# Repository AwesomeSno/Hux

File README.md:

# Hux

A desktop AI smart home companion built with an ESP32-S3, featuring an animated expressive face display, an addressable RGB status ring, dual I2S voice I/O, and native local integration with Home Assistant. Inspired by Jarvis from Iron Man.

---

## What is this?

Most smart home speakers on the market are completely lifeless: they are just boring black plastic pucks sitting on your desk that listen to you with zero personality and no visual feedback beyond a single blinking LED.

For Hack Club's Half Life, I wanted to build something with actual life and presence on my desk: **Hux**. It's a custom desktop hardware companion powered by an ESP32-S3 microcontroller with a crisp color IPS display running expressive animated eyes and reactive facial emotions. 

When you speak to Hux or trigger automations around your room, it talks back, controls your Home Assistant entities (lights, plugs, AC, media) over local Wi-Fi, and dynamically switches its screen into a live telemetry HUD showing room sensor readings, weather, or device toggles.

---

## How it works

1. **Expressive Face & Telemetry Display**: A 1.69" / 2.0" ST7789 IPS LCD (240×280) sits in the center of the board, rendering smooth animated eye expressions (idle blinking, attentive listening, thinking, and speaking waveforms). When you ask about your room or devices, the screen smoothly docks into live Home Assistant glance cards.
2. **Arc-Reactor Status Halo**: A circular ring of 8 addressable RGB NeoPixels encircles the display bezel. It pulses cyan when listening, spins amber when thinking, and flashes red on sensor alerts, giving the desk unit a real presence.
3. **Local Home Assistant Integration**: Hux talks directly to Home Assistant using native WebSockets and REST APIs over local Wi-Fi. No slow cloud hops, no proprietary subscriptions: just instant local control over lights, switches, and smart entities.
4. **I2S Digital Voice Pipeline**: For voice input, an INMP441 digital MEMS microphone samples audio through a front-facing acoustic sound port drilled through the PCB. For voice replies, a MAX98357A I2S Class-D DAC amplifier powers an onboard 3W micro speaker.
5. **72mm Desktop Form Factor**: The whole system is packaged onto a 72mm × 72mm 2-layer PCB with rounded corners and M3 mounting holes, powered cleanly over USB-C.

---

## Hardware Architecture

| Component | Part / Spec | Role |
|---|---|---|
| **MCU** | ESP32-S3-WROOM-1 (16MB Flash, 8MB PSRAM) | Dual-core 240MHz controller handling Wi-Fi, display, and dual I2S audio |
| **Display** | 1.69" or 2.0" ST7789 IPS SPI LCD (240×280) | Animated vector face and smart home telemetry cards |
| **Microphone** | INMP441 I2S Digital MEMS Mic | High-SNR voice input with front acoustic port |
| **Audio Out** | MAX98357A I2S Class-D DAC + 3W 4Ω Speaker | Voice synthesis and feedback playback |
| **Halo Lighting** | 8x SK6812 MINI-E Addressable RGB LEDs | Circular Arc-Reactor status glow |
| **Power & Circuit** | USB-C 16-pin, TLV75533 3.3V LDO, USBLC6-2SC6 ESD | Clean desktop USB 5V power and transient ESD protection |
| **Dimensions** | 72mm × 72mm × 1.6mm FR4 (6mm corner radii) | Standard M3 standoff mounting holes |

---

## Schematic & Hardware Design

The hardware is designed as a clean 2-layer board in KiCad 10:

All hardware design and manufacturing files are located in [`kicad/`](kicad/):
- Full Project: [`kicad/hux.kicad_pro`](kicad/hux.kicad_pro)
- Schematic: [`kicad/hux.kicad_sch`](kicad/hux.kicad_sch) (Printable: [`kicad/hux_schematic.pdf`](kicad/hux_schematic.pdf))
- PCB Layout: [`kicad/hux.kicad_pcb`](kicad/hux.kicad_pcb)
- Bill of Materials: [`kicad/bom.csv`](kicad/bom.csv) (JLCPCB pre-formatted with LCSC parts)
- Pick & Place: [`kicad/cpl.csv`](kicad/cpl.csv)
- Production Gerbers: [`kicad/hux_gerbers.zip`](kicad/hux_gerbers.zip)

---

## Components & Bill of Materials

| Item | Part / Designation | Supplier Code (LCSC / Mfg) | Package | Qty | Role |
|---|---|---|---|---|---|
| **Microcontroller** | ESP32-S3-WROOM-1-N16R8 | LCSC: C5180337 | SMD Module | 1 | 240MHz dual-core MCU, 16MB Flash, 8MB PSRAM, Wi-Fi & BLE |
| **Color IPS Display** | ST7789 1.69" / 2.0" IPS LCD | LCSC: C2903565 / ST7789V | 8-Pin Header / SPI | 1 | Expressive face animations & telemetry dashboard |
| **Digital MEMS Mic** | INMP441 | LCSC: C444583 | SMD Acoustic | 1 | Omnidirectional I2S microphone for voice commands |
| **Audio Amplifier** | MAX98357AETE+T | LCSC: C268261 | QFN-16 | 1 | 3.2W Mono Class-D I2S DAC amplifier |
| **Micro Speaker** | 4Ω 3W Cavity Speaker | JST-PH 2.0mm / C131337 | 28mm / 31mm | 1 | Voice responses and sound effects |
| **Arc-Reactor Halo** | SK6812 MINI-E | LCSC: C2890040 | SMD-3535 | 8 | Circular addressable RGB NeoPixels for status cues |
| **Voltage Regulator** | TLV75533PDBVR | LCSC: C397683 | SOT-23-5 | 1 | Low-dropout 3.3V 500mA LDO regulator |
| **ESD Protection** | USBLC6-2SC6 | LCSC: C7519 | SOT-23-6 | 1 | High-speed USB D+/D- transient ESD suppressor |
| **USB-C Receptacle** | TYPE-C-31-M-12 (16-Pin) | LCSC: C165948 | 16-Pin SMD | 1 | 5V DC power and native USB-CDC programming |
| **Tactile Buttons** | TL3342F160QG | LCSC: C318884 | SMD SPST | 2 | Hardware Reset (EN) and Bootloader (IO0) |
| **Ceramic Capacitors** | 10µF 16V X7R (0805) | LCSC: C15849 | 0805 | 3 | Bulk power input/output filters |
| **Decoupling Caps** | 100nF 50V X7R (0805) | LCSC: C14663 | 0805 | 11 | IC supply decoupling & LED smoothing |
| **Resistors** | 5.1kΩ 1% (0805) | LCSC: C17704 | 0805 | 2 | USB-C CC1/CC2 5V pull-downs |
| **Resistors** | 10kΩ 1% (0805) | LCSC: C17414 | 0805 | 3 | Pull-ups for EN, BOOT, SD_MODE |
| **Resistors** | 330Ω 1% (0805) | LCSC: C17632 | 0805 | 1 | NeoPixel DIN data line protection |
| **Telemetry Header** | 4-Pin 2.54mm Header | LCSC: C22548 | 1x04 P2.54mm | 1 | I2C sensor expansion (SDA, SCL, 3V3, GND) |

---

## Firmware & Software Architecture

The firmware is written in modular C++ targeting the ESP32-S3 dual-core microcontroller, supporting both PlatformIO and the Arduino IDE:

- Entry Point: [`firmware/hux_firmware.ino`](firmware/hux_firmware.ino)
- PlatformIO Project: [`firmware/platformio.ini`](firmware/platformio.ini)
- Hardware Pin Config: [`firmware/include/config.h`](firmware/include/config.h)
- 60fps Vector Eye Engine: [`firmware/src/eyes.cpp`](firmware/src/eyes.cpp)
- Arc-Reactor NeoPixel Halo: [`firmware/src/halo.cpp`](firmware/src/halo.cpp)
- Dual I2S Audio Driver (Mic & Amp): [`firmware/src/audio.cpp`](firmware/src/audio.cpp)
- Home Assistant WebSocket Client: [`firmware/src/home_assistant.cpp`](firmware/src/home_assistant.cpp)
- Multithreaded Core Engine: [`firmware/src/main.cpp`](firmware/src/main.cpp)
- Firmware Guide: [`firmware/README.md`](firmware/README.md)

---

## Author

Designed and built by **Harinandan J V** ([@AwesomeSno](https://github.com/AwesomeSno)) for Hack Club's Half Life.

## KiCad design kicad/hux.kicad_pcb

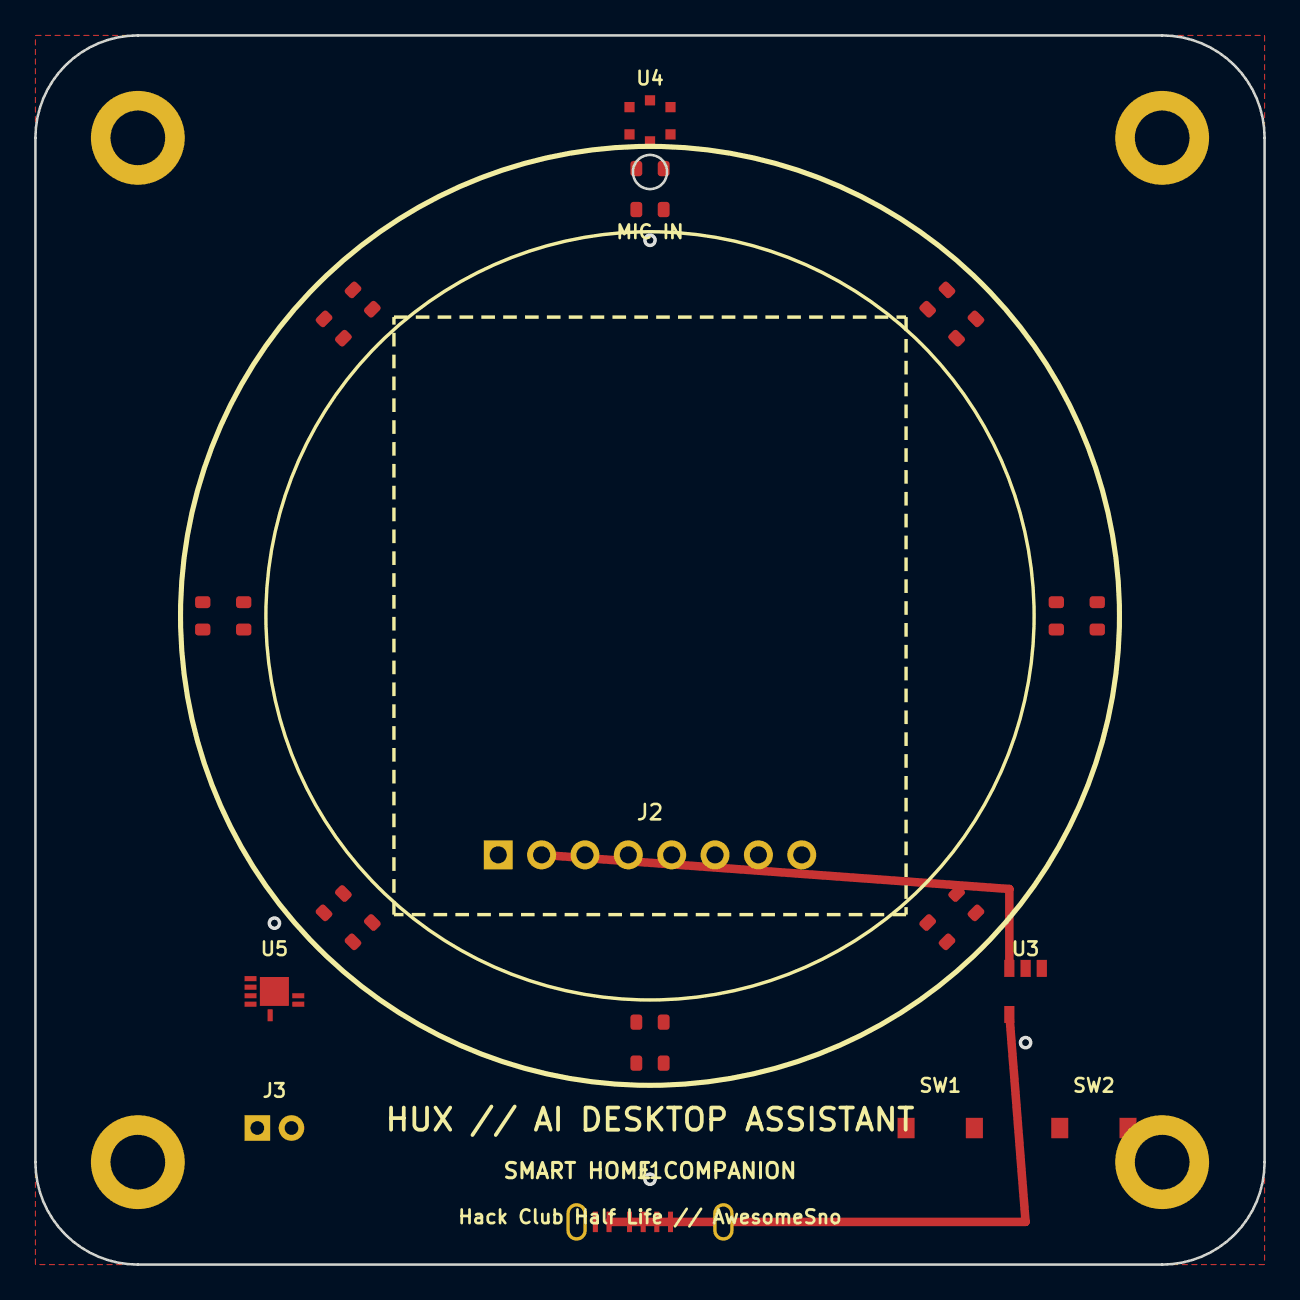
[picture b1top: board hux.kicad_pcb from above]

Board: 2 copper layers, 72.0 x 72.0 mm, 17 parts (1 on the bottom side), 28 nets.

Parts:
J1: USB-C-16P; USB_C_Receptacle_16P
J2: ST7789_1.69_IPS; PinHeader_1x08_P2.54mm_Vertical
J3: SPK_OUT; JST_PH_S2B-PH-K_1x02_P2.00mm_Horizontal
LED1, LED2, LED3, LED4, LED5, LED6, LED7, LED8: SK6812MINI-E; LED_SK6812MINI-E
SW1: RST; SW_SPST_TL3342
SW2: BOOT; SW_SPST_TL3342
U1: ESP32-S3-WROOM-1
U3: TLV75533; SOT-23-5
U4: INMP441
U5: MAX98357A; QFN-16-1EP_3x3mm_P0.5mm_EP1.7x1.7mm

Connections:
+3V3: J2.2, U1.2, U3.5, U4.1
+5V: J1.A4_B9, LED1.1, LED2.1, LED3.1, LED4.1, LED5.1, LED6.1, LED7.1, LED8.1, U3.1, U3.3, U5.7
DISP_BLK: J2.8, U1.23
DISP_CS: J2.7, U1.22
DISP_DC: J2.6, U1.17
DISP_RES: J2.5, U1.18
DISP_SDA: J2.4, U1.19
ESP_EN: SW1.1, U1.3
ESP_IO0: SW2.1, U1.27
GND: J1.A1_B12, J1.A5, J1.B5, J1.SHIELD, J2.1, LED1.3, LED2.3, LED3.3, LED4.3, LED5.3, LED6.3, LED7.3, LED8.3, SW1.2, SW2.2, U1.1, U1.41, U3.2, U4.2, U4.6, U5.4, U5.17
MIC_SCK: U1.6, U4.5
MIC_SD: U1.4, U4.3
MIC_WS: U1.5, U4.4
NEOPIXEL: LED1.4, U1.25
NEO_CASCADE_1: LED1.2, LED2.4
NEO_CASCADE_2: LED2.2, LED3.4
NEO_CASCADE_3: LED3.2, LED4.4
NEO_CASCADE_4: LED4.2, LED5.4
NEO_CASCADE_5: LED5.2, LED6.4
NEO_CASCADE_6: LED6.2, LED7.4
NEO_CASCADE_7: LED7.2, LED8.4
SPK_BCLK: U1.8, U5.2
SPK_DIN: U1.9, U5.1
SPK_LRC: U1.7, U5.3
SPK_OUTN: J3.2, U5.10
SPK_OUTP: J3.1, U5.9
USB_D_N: J1.A7, U1.13
USB_D_P: J1.A6, U1.14

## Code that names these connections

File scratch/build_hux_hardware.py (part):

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    labels += make_label("GND", (150, 115))

    # USB
    labels += make_label("USB_D_P", (95, 45))
    labels += make_label("USB_D_N", (95, 50))
    labels += make_label("USB_D_P", (150, 90))
    labels += make_label("USB_D_N", (150, 95))

    # Display SPI
    labels += make_label("DISP_SCK", (190, 65))
    labels += make_label("DISP_SDA", (190, 70))
    labels += make_label("DISP_RES", (190, 75))
    labels += make_label("DISP_DC",  (190, 80))
    labels += make_label("DISP_CS",  (190, 85))
    labels += make_label("DISP_BLK", (190, 90))

    labels += make_label("DISP_SCK", (230, 56))
    labels += make_label("DISP_SDA", (230, 59))
    labels += make_label("DISP_RES", (230, 61))
    labels += make_label("DISP_DC",  (230, 64))
    labels += make_label("DISP_CS",  (230, 66))
    labels += make_label("DISP_BLK", (230, 69))

    # Mic
    labels += make_label("MIC_SD",  (65, 106))
    labels += make_label("MIC_WS",  (65, 109))
    labels += make_label("MIC_SCK", (65, 112))
    labels += make_label("MIC_SD",  (150, 98))
    labels += make_label("MIC_WS",  (150, 103))
    labels += make_label("MIC_SCK", (150, 108))

    # Speaker
    labels += make_label("SPK_LRC",  (100, 107))
    labels += make_label("SPK_BCLK", (100, 110))
    labels += make_label("SPK_DIN",  (100, 113))
    labels += make_label("SPK_LRC",  (190, 108))
    labels += make_label("SPK_BCLK", (190, 103))
    labels += make_label("SPK_DIN",  (190, 98))

    # NeoPixel
    labels += make_label("NEOPIXEL", (190, 113))
    labels += make_label("NEOPIXEL", (230, 110))

    final_sch = f"""(kicad_sch
	(version 20250114)
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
